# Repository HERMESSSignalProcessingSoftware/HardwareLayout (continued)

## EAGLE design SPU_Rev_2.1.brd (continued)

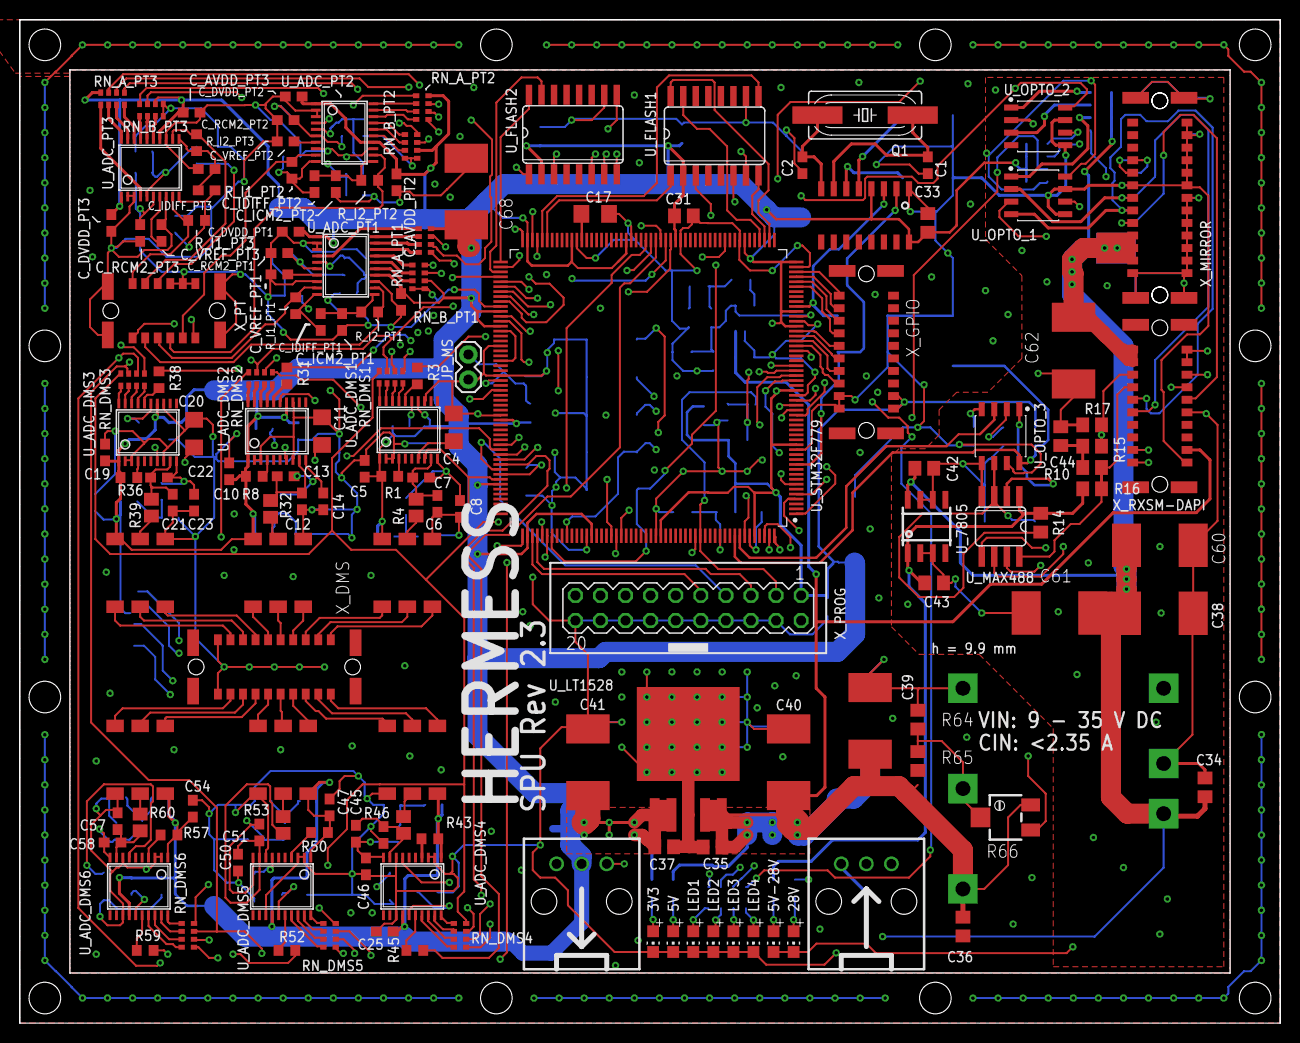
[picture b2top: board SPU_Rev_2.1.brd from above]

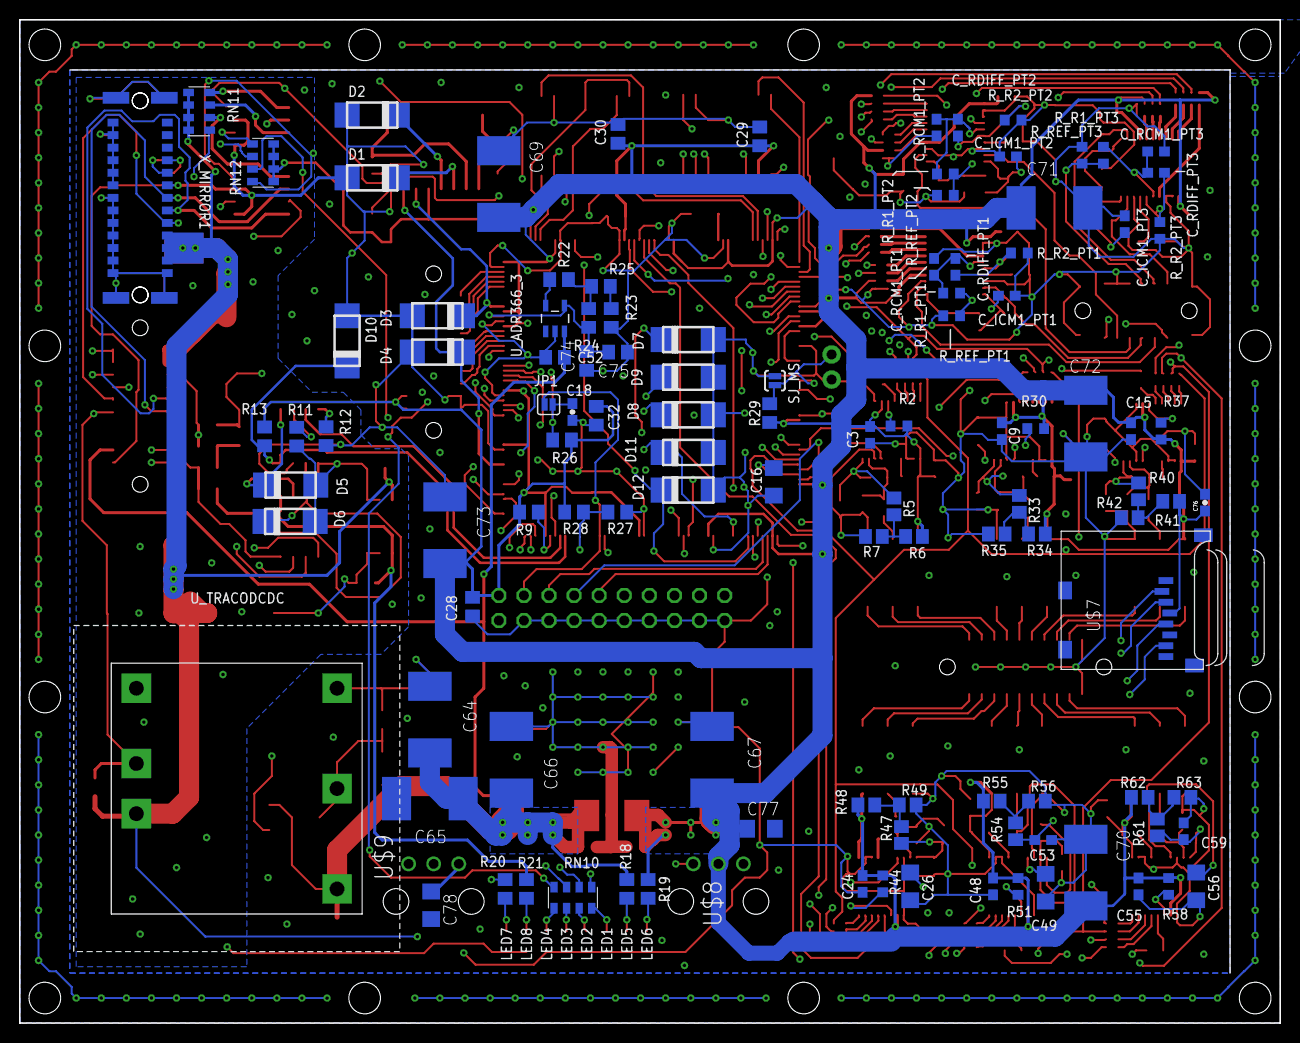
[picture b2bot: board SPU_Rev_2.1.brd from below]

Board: 4 copper layers, 127.6 x 101.6 mm, 261 parts (111 on the bottom side), 254 nets.

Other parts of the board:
R64, R65: inf; R0805
R66: inf; RTRIM3224X

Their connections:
5V: R65.1, R66.3; also elsewhere on the board
GND: R64.1, R66.1; also elsewhere on the board
unnamed 101: R64.2, R65.2, R66.2; also elsewhere on the board

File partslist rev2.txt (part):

Partlist

Exported from SPU_Rev_2.1.brd at 06.09.2020 22:08

EAGLE Version 9.6.2 Copyright (c) 1988-2020 Autodesk, Inc.

Assembly variant: 

Part        Value                      Package                    Library              Position (mil)        Orientation

C1          22p                        C0603                      rcl                  (3820 3420)           R270
C2          22p                        C0603                      rcl                  (3320 3420)           R270
C3          100n                       C0603                      rcl                  (1835 2345)           MR270
C4          1u                         C1206                      rcl                  (1930 2375)           R90
C5          100n                       C0603                      rcl                  (1575 2210)           R90
C6          100n                       C0603                      rcl                  (1865 2070)           R90
C7          100n                       C0603                      rcl                  (1800 2175)           R0
C8          100n                       C0603                      rcl                  (1955 2050)           R270
C9          100n                       C0603                      rcl                  (1310 2360)           MR270
C10         100n                       C0603                      rcl                  (1035 2200)           R90
C11         1u                         C1206                      rcl                  (1405 2360)           R90
C12         100n                       C0603                      rcl                  (1325 2080)           R90
C13         100n                       C0603                      rcl                  (1260 2180)           R0
C14         100n                       C0603                      rcl                  (1410 2080)           R270
C15         100n                       C0603                      rcl                  (795 2360)            MR270
C16         2.2u                       C1206                      rcl                  (2218.92347 2157.87844) MR90
C17         2.2u                       C1206                      rcl                  (2494.14948 3226.10925) R180
C18         100n                       0603-CAP                   aSparkFun            (3021.78396 2436.2564) MR270
C19         100n                       C0603                      rcl                  (540 2275)            R90
C20         1u                         C1206                      rcl                  (895 2350)            R90
C21         100n                       C0603                      rcl                  (810 2075)            R90
C22         100n                       C0603                      rcl                  (755 2175)            R0
C23         100n                       C0603                      rcl                  (895 2075)            R270
C24         100n                       C0603                      rcl                  (1865 555)            MR270
C25         100n                       C0603                      rcl                  (1655 365)            R180
C26         1u                         C1206                      rcl                  (1675 545)            MR270
C27         100n                       C0603                      rcl                  (1650 750)            R90
C28         100n                       C0805                      rcl                  (3420 1660)           MR270
C29         100n                       C0805                      rcl                  (2275 3535)           MR90
C30         100n                       C0805                      rcl                  (2840 3545)           MR90
C31         100n                       C0805                      rcl                  (2847.703 3218.18024) R0
C32         100n                       C0805                      rcl                  (2926.78396 2421.2564) MR270
C33         100n                       C0805                      rcl                  (3820 3190)           R90
C34         100n                       C0805                      rcl                  (4925 940)            R270
C35         100n                       C0805                      rcl                  (2962 702)            R0
C36         100n                       C0805                      rcl                  (3790 460)            R90
C37         100n                       C0805                      rcl                  (2769 703)            R180
C38         10u                        E/7260-38W                 rcl                  (4745 1634)           R180
C39         10u                        E/7260-38W                 rcl                  (3590 1025)           R270
C40         10u                        E/7260-38W                 rcl                  (3265 1040)           R270
C41         10u                        E/7260-38W                 rcl                  (2465 1040)           R270
C42         100n                       C0805                      rcl                  (3806 2212)           R180
C43         100n                       C0805                      rcl                  (3845 1755)           R0
C44         ~0                         C0805                      rcl                  (4350 2340)           R90
C45         100n                       C0603                      rcl                  (1540 755)            R270
C46         100n                       C0603                      rcl                  (1580 625)            R270
C47         100n                       C0603                      rcl                  (1435 860)            R90
C48         100n                       C0603                      rcl                  (1345 545)            MR270
C49         1u                         C1206                      rcl                  (1135 540)            MR270
C50         100n                       C0603                      rcl                  (1070 640)            R90
C51         100n                       C0603                      rcl                  (1155 760)            R90
C52         10n                        C0805                      rcl                  (3091.08612 2654.11196) MR0
C53         100n                       C0603                      rcl                  (1145 730)            MR0
C54         100n                       C0603                      rcl                  (890 855)             R90
C55         100n                       C0603                      rcl                  (765 545)             MR270
C56         1u                         C1206                      rcl                  (535 545)             MR270
C57         100n                       C0603                      rcl                  (590 805)             R270
C58         100n                       C0603                      rcl                  (570 720)             R180
C59         100n                       C0603                      rcl                  (585 765)             MR90
C60         10u                        E/7260-38W                 rcl                  (4745 1905)           R180
C61         10u                        E/7260-38W                 rcl                  (4345 1635)           R0
C62         10u                        E/7260-38W                 rcl                  (4401 2681)           R90
C63         10u                        E/7260-38W                 rcl                  (3590 620)            R90
C64         10u                        E/7260-38W                 rcl                  (3590 1035)           MR270
C65         10u                        E/7260-38W                 rcl                  (3590 615)            MR90
C66         10u                        E/7260-38W                 rcl                  (3265 1050)           MR270
C67         10u                        E/7260-38W                 rcl                  (2465 1050)           MR270
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
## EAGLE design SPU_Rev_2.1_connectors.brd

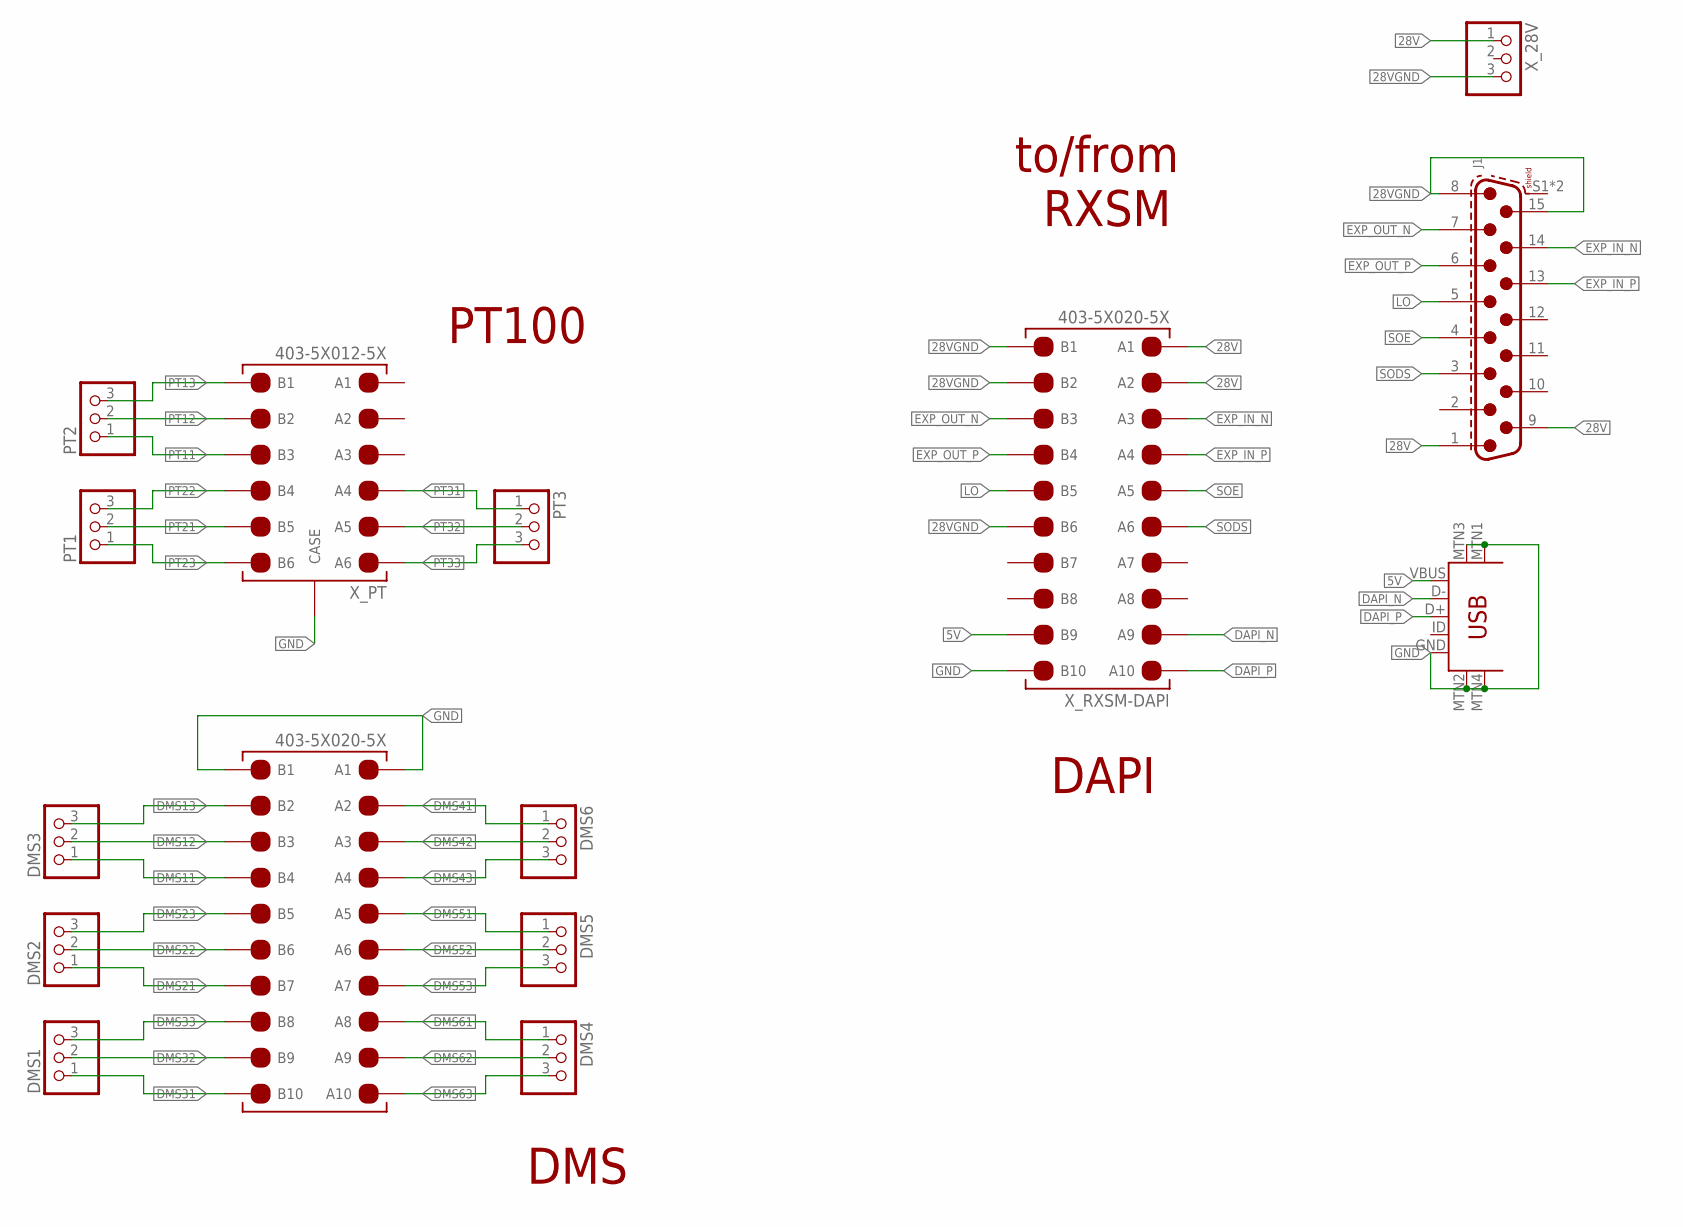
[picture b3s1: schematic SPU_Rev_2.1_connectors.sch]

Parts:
DMS1, DMS2, DMS3, DMS4, DMS5, DMS6: PINHD-1X3; 1X03
J1: 6180XX211721_618015211721; 618015211721
PT1, PT2, PT3: PINHD-1X3; 1X03
U$1: USB-MINIB-5PIN; USB-MINIB
X_28V: PINHD-1X3; 1X03
X_DMS: 403-5X020-5X
X_PT: 403-5X012-5X
X_RXSM-DAPI: 403-5X020-5X

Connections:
5V: U$1.VBUS, X_RXSM-DAPI.P$B9 (B9)
28V: J1.1, J1.9, X_28V.1, X_RXSM-DAPI.P$A1 (A1), X_RXSM-DAPI.P$A2 (A2)
28VGND: J1.8, J1.15, X_28V.3, X_RXSM-DAPI.P$B1 (B1), X_RXSM-DAPI.P$B2 (B2), X_RXSM-DAPI.P$B6 (B6)
DAPI_N: U$1.D-, X_RXSM-DAPI.P$A9 (A9)
DAPI_P: U$1.D+, X_RXSM-DAPI.P$A10 (A10)
DMS11: DMS3.1, X_DMS.P$B4 (B4)
DMS12: DMS3.2, X_DMS.P$B3 (B3)
DMS13: DMS3.3, X_DMS.P$B2 (B2)
DMS21: DMS2.1, X_DMS.P$B7 (B7)
DMS22: DMS2.2, X_DMS.P$B6 (B6)
DMS23: DMS2.3, X_DMS.P$B5 (B5)
DMS31: DMS1.1, X_DMS.P$B10 (B10)
DMS32: DMS1.2, X_DMS.P$B9 (B9)
DMS33: DMS1.3, X_DMS.P$B8 (B8)
DMS41: DMS6.1, X_DMS.P$A2 (A2)
DMS42: DMS6.2, X_DMS.P$A3 (A3)
DMS43: DMS6.3, X_DMS.P$A4 (A4)
DMS51: DMS5.1, X_DMS.P$A5 (A5)
DMS52: DMS5.2, X_DMS.P$A6 (A6)
DMS53: DMS5.3, X_DMS.P$A7 (A7)
DMS61: DMS4.1, X_DMS.P$A8 (A8)
DMS62: DMS4.2, X_DMS.P$A9 (A9)
DMS63: DMS4.3, X_DMS.P$A10 (A10)
EXP_IN_N: J1.14, X_RXSM-DAPI.P$A3 (A3)
EXP_IN_P: J1.13, X_RXSM-DAPI.P$A4 (A4)
EXP_OUT_N: J1.7, X_RXSM-DAPI.P$B3 (B3)
EXP_OUT_P: J1.6, X_RXSM-DAPI.P$B4 (B4)
GND: U$1.GND, U$1.MTN1 (MTN2), U$1.MTN2 (MTN3), U$1.MTN3 (MTN1), U$1.MTN4, X_DMS.P$A1 (A1), X_DMS.P$B1 (B1), X_PT.P$BL1 (CASE), X_PT.P$BL2 (CASE), X_PT.P$BL3 (CASE), X_PT.P$BL4 (CASE), X_RXSM-DAPI.P$B10 (B10)
LO: J1.5, X_RXSM-DAPI.P$B5 (B5)
PT11: PT2.1, X_PT.P$B3 (B3)
PT12: PT2.2, X_PT.P$B2 (B2)
PT13: PT2.3, X_PT.P$B1 (B1)
PT21: PT1.2, X_PT.P$B5 (B5)
PT22: PT1.3, X_PT.P$B4 (B4)
PT23: PT1.1, X_PT.P$B6 (B6)
PT31: PT3.1, X_PT.P$A4 (A4)
PT32: PT3.2, X_PT.P$A5 (A5)
PT33: PT3.3, X_PT.P$A6 (A6)
SODS: J1.3, X_RXSM-DAPI.P$A6 (A6)
SOE: J1.4, X_RXSM-DAPI.P$A5 (A5)

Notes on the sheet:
DMS
PT100
DAPI
to/from RXSM

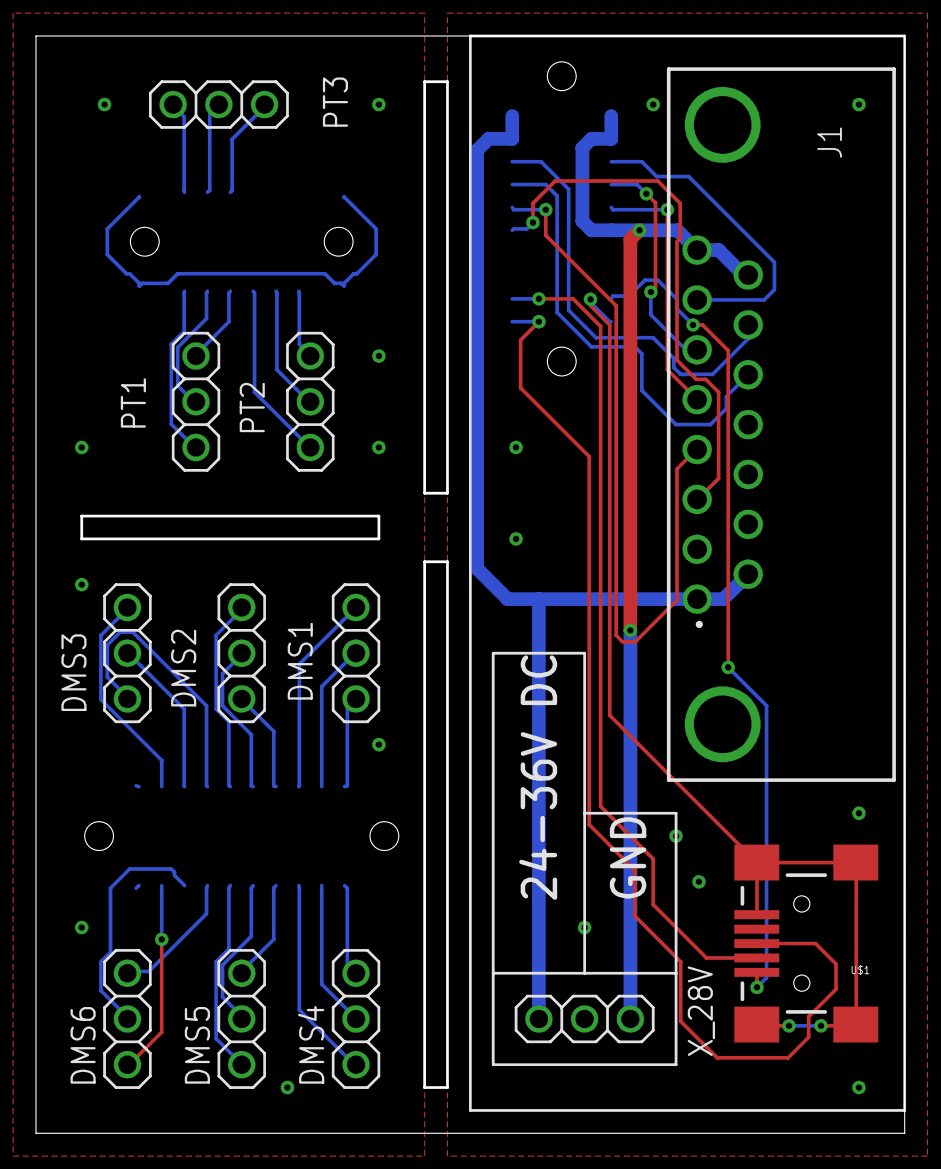
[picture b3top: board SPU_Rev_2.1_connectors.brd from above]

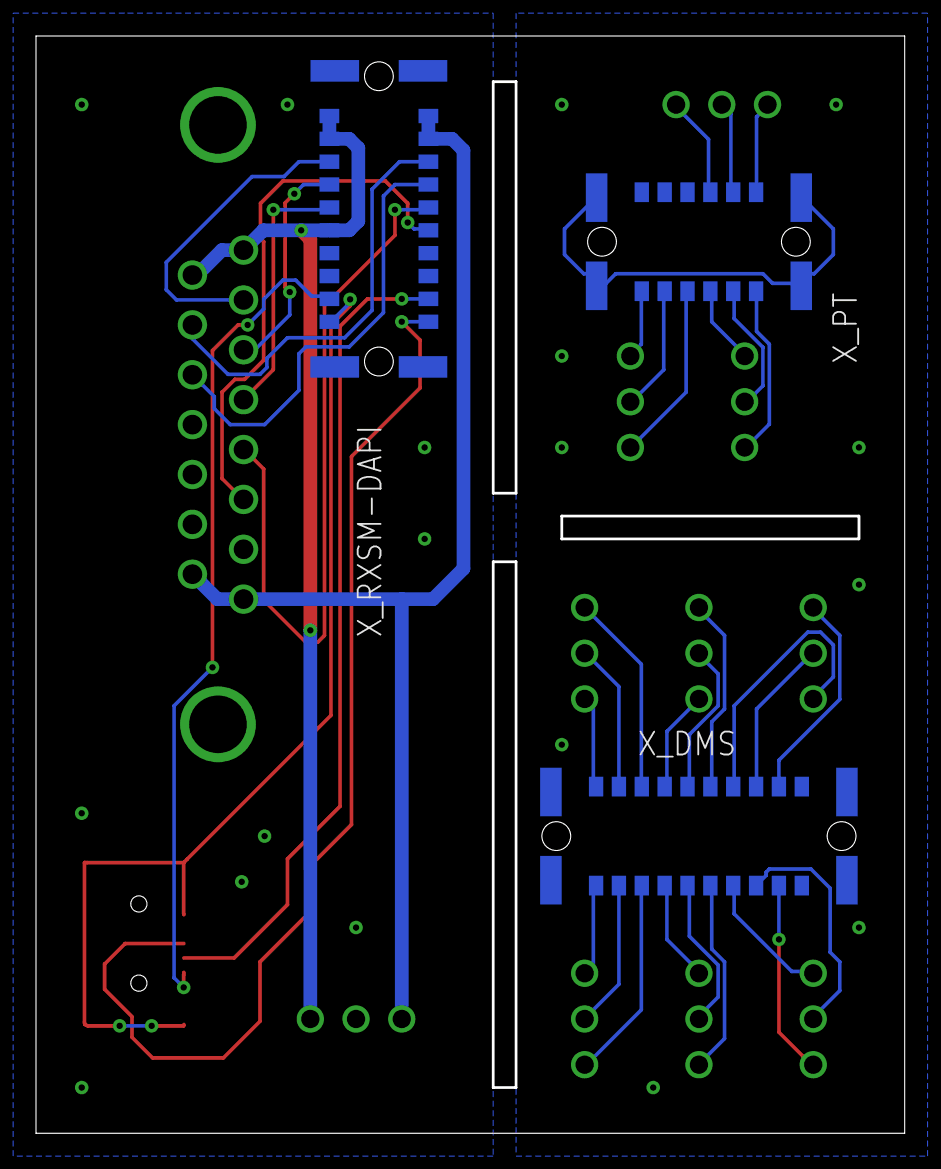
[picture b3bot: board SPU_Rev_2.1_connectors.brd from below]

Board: 2 copper layers, 48.3 x 61.0 mm, 15 parts (3 on the bottom side), 40 nets.

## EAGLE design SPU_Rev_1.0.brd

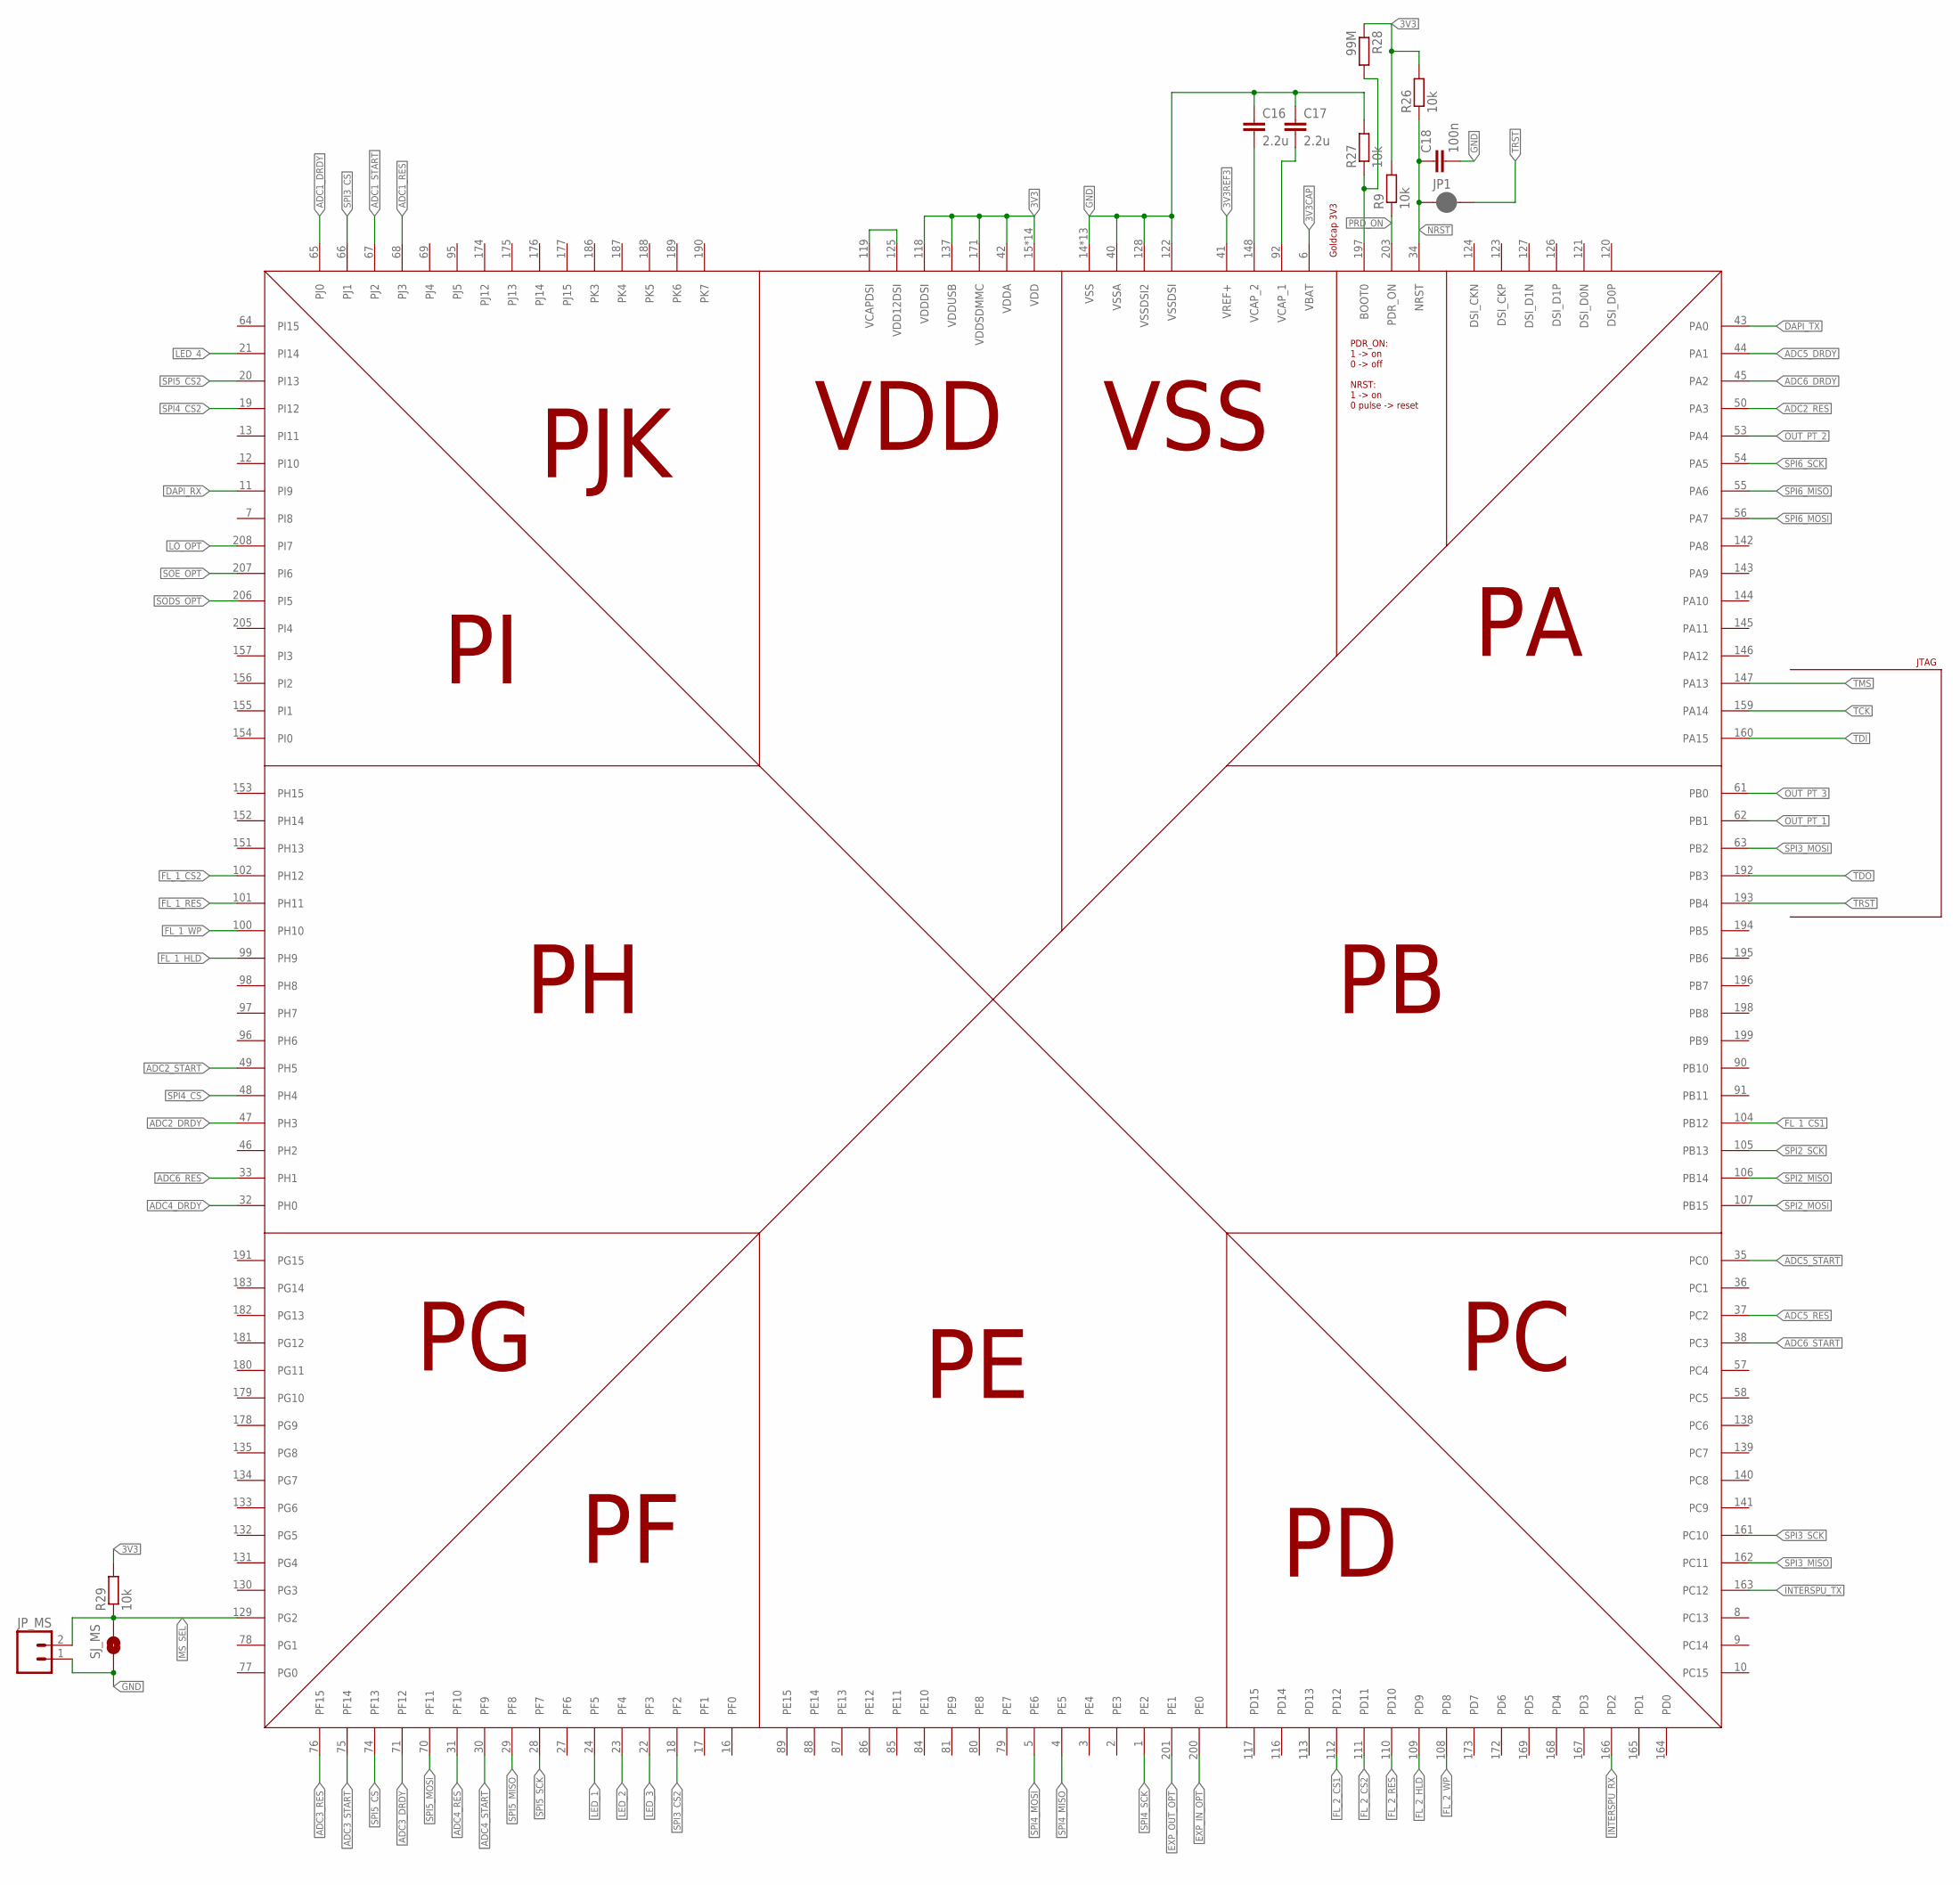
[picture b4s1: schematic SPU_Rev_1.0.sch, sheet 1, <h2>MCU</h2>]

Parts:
C16, C17: 2.2u; C1206
C18: 100n; 0603-CAP
JP1: JUMPER-SMT_2_NC_PASTE_SILK; SMT-JUMPER_2_NC_PASTE_SILK
JP_MS: M02PTH; 1X02
R9, R26, R27, R29: 10k; R0805
R28: 99M; R0805
SJ_MS: SOLDERJUMPERNO; SJ_2S-NO
U9: STM32F77XXXLQFP208; QFP50P3060X3060X385-208

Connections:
3V3: R9.2, R26.2, R28.1, R29.2, U9.15 (VDD), U9.26 (VDD), U9.39 (VDD), U9.42 (VDDA), U9.52 (VDD), U9.59 (VDD), U9.73 (VDD), U9.83 (VDD), U9.94 (VDD), U9.103 (VDD), U9.115 (VDD), U9.118 (VDDDSI), U9.137 (VDDUSB), U9.150 (VDD), U9.158 (VDD), U9.171 (VDDSDMMC), U9.185 (VDD), U9.204 (VDD); also elsewhere on the board
3V3CAP: U9.6 (VBAT)
3V3REF3: U9.41 (VREF+); also elsewhere on the board
ADC1_DRDY: U9.65 (PJ0); also elsewhere on the board
ADC1_RES: U9.68 (PJ3); also elsewhere on the board
ADC1_START: U9.67 (PJ2); also elsewhere on the board
ADC2_DRDY: U9.47 (PH3); also elsewhere on the board
ADC2_RES: U9.50 (PA3); also elsewhere on the board
ADC2_START: U9.49 (PH5); also elsewhere on the board
ADC3_DRDY: U9.71 (PF12); also elsewhere on the board
ADC3_RES: U9.76 (PF15); also elsewhere on the board
ADC3_START: U9.75 (PF14); also elsewhere on the board
ADC4_DRDY: U9.32 (PH0); also elsewhere on the board
ADC4_RES: U9.31 (PF10); also elsewhere on the board
ADC4_START: U9.30 (PF9); also elsewhere on the board
ADC5_DRDY: U9.44 (PA1); also elsewhere on the board
ADC5_RES: U9.37 (PC2); also elsewhere on the board
ADC5_START: U9.35 (PC0); also elsewhere on the board
ADC6_DRDY: U9.45 (PA2); also elsewhere on the board
ADC6_RES: U9.33 (PH1); also elsewhere on the board
ADC6_START: U9.38 (PC3); also elsewhere on the board
DAPI_RX: U9.11 (PI9); also elsewhere on the board
DAPI_TX: U9.43 (PA0); also elsewhere on the board
EXP_IN_OPT: U9.200 (PE0); also elsewhere on the board
EXP_OUT_OPT: U9.201 (PE1); also elsewhere on the board
FL_1_CS1: U9.104 (PB12); also elsewhere on the board
FL_1_CS2: U9.102 (PH12); also elsewhere on the board
FL_1_HLD: U9.99 (PH9); also elsewhere on the board
FL_1_RES: U9.101 (PH11); also elsewhere on the board
FL_1_WP: U9.100 (PH10); also elsewhere on the board
FL_2_CS1: U9.112 (PD12); also elsewhere on the board
FL_2_CS2: U9.111 (PD11); also elsewhere on the board
FL_2_HLD: U9.109 (PD9); also elsewhere on the board
FL_2_RES: U9.110 (PD10); also elsewhere on the board
FL_2_WP: U9.108 (PD8); also elsewhere on the board
GND: C16.1, C17.1, C18.2, JP_MS.1, R27.2, SJ_MS.1, U9.14 (VSS), U9.25 (VSS), U9.40 (VSSA), U9.51 (VSS), U9.60 (VSS), U9.72 (VSS), U9.82 (VSS), U9.93 (VSS), U9.114 (VSS), U9.122 (VSSDSI), U9.128 (VSSDSI2), U9.136 (VSS), U9.149 (VSS), U9.170 (VSS), U9.184 (VSS), U9.202 (VSS); also elsewhere on the board
INTERSPU_RX: U9.166 (PD2); also elsewhere on the board
INTERSPU_TX: U9.163 (PC12); also elsewhere on the board
LED_1: U9.24 (PF5); also elsewhere on the board
LED_2: U9.23 (PF4); also elsewhere on the board
LED_3: U9.22 (PF3); also elsewhere on the board
LED_4: U9.21 (PI14); also elsewhere on the board
LO_OPT: U9.208 (PI7); also elsewhere on the board
MS_SEL: JP_MS.2, R29.1, SJ_MS.2, U9.129 (PG2)
unnamed: C16.2, U9.148 (VCAP_2)
unnamed: C17.2, U9.92 (VCAP_1)
unnamed: U9.119 (VCAPDSI), U9.125 (VDD12DSI)
unnamed: R27.1, R28.2, U9.197 (BOOT0)
NRST: C18.1, JP1.1, R26.1, U9.34 (NRST)
OUT_PT_1: U9.62 (PB1); also elsewhere on the board
OUT_PT_2: U9.53 (PA4); also elsewhere on the board
OUT_PT_3: U9.61 (PB0); also elsewhere on the board
PRD_ON: R9.1, U9.203 (PDR_ON)
SODS_OPT: U9.206 (PI5); also elsewhere on the board
SOE_OPT: U9.207 (PI6); also elsewhere on the board
SPI2_MISO: U9.106 (PB14); also elsewhere on the board
SPI2_MOSI: U9.107 (PB15); also elsewhere on the board
SPI2_SCK: U9.105 (PB13); also elsewhere on the board
SPI3_CS: U9.66 (PJ1); also elsewhere on the board
SPI3_CS2: U9.18 (PF2); also elsewhere on the board
SPI3_MISO: U9.162 (PC11); also elsewhere on the board
SPI3_MOSI: U9.63 (PB2); also elsewhere on the board
SPI3_SCK: U9.161 (PC10); also elsewhere on the board
SPI4_CS: U9.48 (PH4); also elsewhere on the board
SPI4_CS2: U9.19 (PI12); also elsewhere on the board
SPI4_MISO: U9.4 (PE5); also elsewhere on the board
SPI4_MOSI: U9.5 (PE6); also elsewhere on the board
SPI4_SCK: U9.1 (PE2); also elsewhere on the board
SPI5_CS: U9.74 (PF13); also elsewhere on the board
SPI5_CS2: U9.20 (PI13); also elsewhere on the board
SPI5_MISO: U9.29 (PF8); also elsewhere on the board
SPI5_MOSI: U9.70 (PF11); also elsewhere on the board
SPI5_SCK: U9.28 (PF7); also elsewhere on the board
SPI6_MISO: U9.55 (PA6); also elsewhere on the board
SPI6_MOSI: U9.56 (PA7); also elsewhere on the board
SPI6_SCK: U9.54 (PA5); also elsewhere on the board
TCK: U9.159 (PA14); also elsewhere on the board
TDI: U9.160 (PA15); also elsewhere on the board
TDO: U9.192 (PB3); also elsewhere on the board
TMS: U9.147 (PA13); also elsewhere on the board
TRST: JP1.2, U9.193 (PB4); also elsewhere on the board

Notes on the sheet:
JTAG
Goldcap 3V3
PDR_ON: 1 -> on 0 -> off NRST: 1 -> on 0 pulse -> reset
